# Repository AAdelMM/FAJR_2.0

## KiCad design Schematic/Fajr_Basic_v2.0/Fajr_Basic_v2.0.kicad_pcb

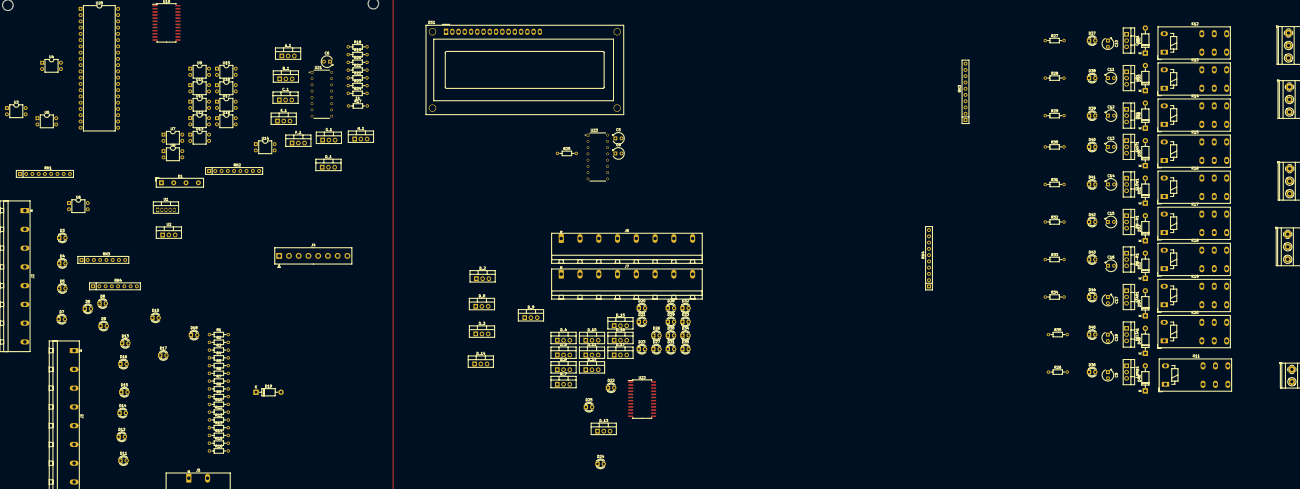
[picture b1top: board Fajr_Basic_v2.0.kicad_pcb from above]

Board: 2 copper layers, 187 parts (0 on the bottom side), 173 nets, no tracks yet.

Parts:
A_1: BD681; TO-220-3_Vertical
B_1: BD681; TO-220-3_Vertical
C5, C6, C8, C9, C10, C11, C12, C13, C14, C15, C16, C17, C18: 104; CP_Radial_Tantal_D4.5mm_P2.50mm
C_1: BD681; TO-220-3_Vertical
Cam1: BD681; TO-220-3_Vertical
D1: BR3A; Diode_Bridge_19.0x3.5x10.0mm_P5.0mm
D3, D4, D5, D6, D7, D8, D9, D10, D11, D12, D13, D14, D15, D16, D17, D18, D20, D21, D22, D23, D24, D25, D26, D27, D28, D29, D30, D31, D32, D33, D34, D35, D36, D37, D38, D39, D40, D41, D42, D43, D44, D45: LED; LED_D3.0mm
D19, D53: 1N4001; D_DO-41_SOD81_P10.16mm_Horizontal
D46, D47, D48, D49, D50, D51, D52, D54, D55: D_DO-41_SOD81_P10.16mm_Horizontal
DELTA1: BD681; TO-220-3_Vertical
DN1: BD681; TO-220-3_Vertical
DS1: WC1602A
D_1, D_2, D_3, D_4, D_5, D_6, D_7, D_8, D_9, D_10, D_11, D_12, D_13, D_14, D_15, D_16, D_17: BD681; TO-220-3_Vertical
E_1: BD681; TO-220-3_Vertical
FAST1: BD681; TO-220-3_Vertical
F_1: BD681; TO-220-3_Vertical
G_1: BD681; TO-220-3_Vertical
H_1: BD681; TO-220-3_Vertical
J2, J3, J6, J7: Screw_Terminal_01x08; PhoenixContact_GMSTBA_2,5_8-G-7,62_1x08_P7.62mm_Horizontal
J4: Display; TE_826576-8_1x08_P3.96mm_Vertical
J5: Screw_Terminal_01x02; PhoenixContact_GMSTB_2,5_2-GF-7,62_1x02_P7.62mm_Horizontal_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
J8: Screw_Terminal_01x02; TerminalBlock_Phoenix_MKDS-1,5-2_1x02_P5.00mm_Horizontal
J9, J10, J11, J12: Screw_Terminal_01x03; TerminalBlock_Phoenix_MKDS-1,5-3-5.08_1x03_P5.08mm_Horizont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
K11: Light; Relay_DPDT_Schrack-RT2-FormC_RM5mm
K12: CAM; Relay_DPDT_Schrack-RT2-FormC_RM5mm
K13: UP; Relay_DPDT_Schrack-RT2-FormC_RM5mm
K14: DN; Relay_DPDT_Schrack-RT2-FormC_RM5mm
K15: Fast; Relay_DPDT_Schrack-RT2-FormC_RM5mm
K16: Slow; Relay_DPDT_Schrack-RT2-FormC_RM5mm
K17: A_UP; Relay_DPDT_Schrack-RT2-FormC_RM5mm
K18: A_DN; Relay_DPDT_Schrack-RT2-FormC_RM5mm
K19, K20: RTE2xxxx; Relay_DPDT_Schrack-RT2-FormC_RM5mm
Lamp1: BD681; TO-220-3_Vertical
PH-N1: BD681; TO-220-3_Vertical
PH-R1: BD681; TO-220-3_Vertical
R1, R2, R3, R4, R5, R6, R7, R8, R9, R10, R11, R12, R13, R14, R15, R16: 1.2k; R_Axial_DIN0204_L3.6mm_D1.6mm_P7.62mm_Horizontal
R17, R18, R19, R20, R21, R22, R23, R24, R26, R27, R28, R29, R30, R31, R32, R33, R34, R35: 1k; R_Axial_DIN0204_L3.6mm_D1.6mm_P7.62mm_Horizontal
R25: 5.1k; R_Axial_DIN0204_L3.6mm_D1.6mm_P7.62mm_Horizontal
RN1, RN2: 2.2k; R_Array_SIP9
RN3, RN4: 820R; R_Array_SIP10
RN3#2, RN4#2: 1k; R_Array_SIP8
SLOW1: BD681; TO-220-3_Vertical
STAR1: BD681; TO-220-3_Vertical
U1: LM2576; TO-220-5_Vertical
U2: LM7805_TO220; TO-220-3_Vertical
U3, U4, U5, U6, U7, U8, U9, U10, U11, U12, U13, U14, U15, U16, U17, U18: PC817; DIP-4_W7.62mm
U19, U22: CD74HC4067M; SOIC-24W_7.5x15.4mm_P1.27mm
U20: ATmega644-20P; DIP-40_W15.24mm
U21, U23: CD4094BE; DIP794W45P254L1969H508Q16
UP1: BD681; TO-220-3_Vertical

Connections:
/7SEG/+5V: C5.1, C6.1, C8.1, DS1.2 (VDD), RN1.1 (common), RN2.1 (common), U2.3 (VO), U19.24 (VCC), U21.15 (OUT_EN), U21.16 (VDD), U23.15 (OUT_EN), U23.16 (VDD)
/7SEG/PD5: U20.19 (PD5), U21.2 (DATA)
/7SEG/PD6: U20.20 (PD6), U21.3 (CLOCK), U23.3 (CLOCK)
/7SEG/PD7: U20.21 (PD7), U21.1 (STRB), U23.1 (STRB)
/7SEG/Q`S: R25.2, U21.10 (QS), U23.2 (DATA)
/CALLS_SINALS/PC7: U20.29 (PC7), U22.1 (COM)
/LCD/PA3: DS1.6 (E), U20.37 (PA3)
/LCD/PD4: DS1.4 (RS), U19.10 (S0), U20.36 (PA4)
/MCU_MAIN/PA5: U19.11 (S1), U20.35 (PA5)
/MCU_MAIN/PA6: U19.14 (S2), U20.34 (PA6)
/MCU_MAIN/PA7: U19.13 (S3), U20.33 (PA7)
/MCU_MAIN/PC6: U19.1 (COM), U20.28 (PC6)
/Movement/+12V: C9.2, C10.2, C11.2, C12.2, C13.2, C14.2, C15.2, C16.2, C17.2, C18.2, D46.1 (K), D47.1 (K), D48.1 (K), D49.1 (K), D50.1 (K), D51.1 (K), D52.1 (K), D53.1 (K), D54.1 (K), D55.1 (K), K11.A1, K12.A1, K13.A1, K14.A1, K15.A1, K16.A1, K17.A1, K18.A1, K19.A1, K20.A1, R26.1, R27.1, R28.1, R29.1, R30.1, R31.1, R32.1, R33.1, R34.1, R35.1, U1.4 (FB), U2.1 (VI)
/Power_circuit/+24: D1.3 (+), D19.2 (A), U1.1 (VIN)
AUX: RN2.5 (R4), U14.4, U19.5 (I4)
DCL: RN2.4 (R3), U13.4, U19.3 (I6)
DNL: RN1.9 (R8), U10.4, U19.20 (I11)
DOP: RN2.3 (R2), U12.4, U19.4 (I5)
FIRE: RN2.6 (R5), U15.4, U19.2 (I7)
FRK: RN1.6 (R5), U7.4, U19.23 (I8)
GND: A_1.3 (E), B_1.3 (E), C5.2, C6.2, C8.2, C_1.3 (E), Cam1.3 (E), D1.1 (-), DELTA1.3 (E), DN1.3 (E), DS1.1 (VSS), DS1.5 (R/W), D_1.3 (E), D_2.3 (E), D_3.3 (E), D_4.3 (E), D_5.3 (E), D_6.3 (E), D_7.3 (E), D_8.3 (E), D_9.3 (E), D_10.3 (E), D_11.3 (E), D_12.3 (E), D_13.3 (E), D_14.3 (E), D_15.3 (E), D_16.3 (E), D_17.3 (E), E_1.3 (E), FAST1.3 (E), F_1.3 (E), G_1.3 (E), H_1.3 (E), Lamp1.3 (E), PH-N1.3 (E), PH-R1.3 (E), R25.1, SLOW1.3 (E), STAR1.3 (E), U1.3 (GND), U1.5 (~ON/OFF), U2.2 (GND), U3.2, U3.3, U4.2, U4.3, U5.2, U5.3, U6.2, U6.3, U7.2, U7.3, U8.2, U8.3, U9.2, U9.3, U10.2, U10.3, U11.2, U11.3, U12.2, U12.3, U13.2, U13.3, U14.2, U14.3, U15.2, U15.3, U16.2, U16.3, U17.2, U17.3, U18.2, U18.3, U19.12 (GND), U19.15 (~E), U21.8 (VSS), U23.8 (VSS), UP1.3 (E)
LOC: RN1.7 (R6), U8.4, U19.22 (I9)
MTR: RN1.5 (R4), U6.4, U19.18 (I13)
unnamed: A_1.1 (B), R17.2
unnamed: A_1.2 (C), J4.1
unnamed: B_1.1 (B), R18.2
unnamed: B_1.2 (C), J4.2
unnamed: C_1.1 (B), R19.2
unnamed: C_1.2 (C), J4.3
unnamed: C10.1, Cam1.2 (C), D37.1 (K), D47.2 (A), K12.A2
unnamed: D3.2 (A), J2.8
unnamed: D3.1 (K), R1.1
unnamed: D4.2 (A), J2.7
unnamed: D4.1 (K), R2.1
unnamed: D5.2 (A), J2.6
unnamed: D5.1 (K), R3.1
unnamed: D6.2 (A), J2.5
unnamed: D6.1 (K), R4.1
unnamed: D7.2 (A), J2.4
unnamed: D7.1 (K), R5.1
unnamed: D8.2 (A), J2.3
unnamed: D8.1 (K), R6.1
unnamed: D9.2 (A), J2.2
unnamed: D9.1 (K), R7.1
unnamed: D10.2 (A), J2.1
unnamed: D10.1 (K), R8.1
unnamed: D11.2 (A), J3.8
unnamed: D11.1 (K), R9.1
unnamed: D12.2 (A), J3.7
unnamed: D12.1 (K), R10.1
unnamed: D13.2 (A), J3.6
unnamed: D13.1 (K), R11.1
unnamed: D14.2 (A), J3.5
unnamed: D14.1 (K), R12.1
unnamed: D15.2 (A), J3.4
unnamed: D15.1 (K), R13.1
unnamed: D16.2 (A), J3.3
unnamed: D16.1 (K), R14.1
unnamed: D17.2 (A), J3.2
unnamed: D17.1 (K), R15.1
unnamed: D18.2 (A), J3.1
unnamed: D18.1 (K), R16.1
unnamed: D19.1 (K), J5.1
unnamed: D20.1 (K), D_17.1 (B)
unnamed: D21.1 (K), D_16.1 (B)
unnamed: D22.1 (K), D_15.1 (B)
unnamed: D23.1 (K), D_14.1 (B)
unnamed: D24.1 (K), D_13.1 (B)
unnamed: D25.1 (K), D_12.1 (B)
unnamed: D26.1 (K), D_11.1 (B)
unnamed: D27.1 (K), D_10.1 (B)
unnamed: D28.1 (K), D_9.1 (B)
unnamed: D29.1 (K), D_8.1 (B)
unnamed: D30.1 (K), D_7.1 (B)
unnamed: D31.1 (K), D_6.1 (B)
unnamed: D32.1 (K), D_5.1 (B)
unnamed: D33.1 (K), D_4.1 (B)
unnamed: D34.1 (K), D_3.1 (B)
unnamed: D35.1 (K), D_2.1 (B)
unnamed: D36.2 (A), R26.2
unnamed: C9.1, D36.1 (K), D46.2 (A), K11.A2, Lamp1.2 (C)
unnamed: D37.2 (A), R27.2
unnamed: D38.2 (A), R28.2
unnamed: C11.1, D38.1 (K), D48.2 (A), K13.A2, UP1.2 (C)
unnamed: D39.2 (A), R29.2
unnamed: C12.1, D39.1 (K), D49.2 (A), DN1.2 (C), K14.A2
unnamed: D40.2 (A), R30.2
unnamed: C13.1, D40.1 (K), D50.2 (A), FAST1.2 (C), K15.A2
unnamed: D41.2 (A), R31.2
unnamed: C14.1, D41.1 (K), D51.2 (A), K16.A2, SLOW1.2 (C)
unnamed: D42.2 (A), R32.2
unnamed: C15.1, D42.1 (K), D52.2 (A), K17.A2, PH-N1.2 (C)
unnamed: D43.2 (A), R33.2
unnamed: C16.1, D43.1 (K), D53.2 (A), K18.A2, PH-R1.2 (C)
unnamed: D44.2 (A), R34.2
unnamed: C17.1, D44.1 (K), D54.2 (A), K19.A2, STAR1.2 (C)
unnamed: D45.2 (A), R35.2
unnamed: C18.1, D45.1 (K), D55.2 (A), DELTA1.2 (C), K20.A2
unnamed: DS1.7 (D0), U23.11 (Q8)
unnamed: DS1.8 (D1), U23.12 (Q7)
unnamed: DS1.9 (D2), U23.13 (Q6)
unnamed: DS1.10 (D3), U23.14 (Q5)
unnamed: DS1.11 (D4), U23.7 (Q4)
unnamed: DS1.12 (D5), U23.6 (Q3)
unnamed: DS1.13 (D6), U23.5 (Q2)
unnamed: DS1.14 (D7), U23.4 (Q1)
unnamed: D_1.1 (B), R20.2
unnamed: D_1.2 (C), J4.4
unnamed: E_1.1 (B), R21.2
unnamed: E_1.2 (C), J4.5
unnamed: F_1.1 (B), R22.2
unnamed: F_1.2 (C), J4.6
unnamed: G_1.1 (B), R23.2
unnamed: G_1.2 (C), J4.7
unnamed: H_1.1 (B), R24.2
unnamed: H_1.2 (C), J4.8
unnamed: J8.1, K11.14, K11.24
unnamed: J8.2, K11.11, K11.21
unnamed: J9.1, K12.11, K12.21
unnamed: J9.2, K12.14, K12.24
unnamed: J9.3, K12.12, K12.22
unnamed: J10.1, K13.11, K13.21, K14.11, K14.21
unnamed: J10.2, K13.14, K13.24
unnamed: J10.3, K14.14, K14.24
unnamed: J11.1, K15.11, K15.21, K16.11, K16.21
unnamed: J11.2, K15.14, K15.24
unnamed: J11.3, K16.14, K16.24
unnamed: J12.1, K17.11, K17.21, K18.11, K18.21
unnamed: J12.2, K17.24
unnamed: J12.3, K18.24
unnamed: R1.2, U3.1
unnamed: R2.2, U4.1
unnamed: R3.2, U5.1
unnamed: R4.2, U6.1
unnamed: R5.2, U7.1
unnamed: R6.2, U8.1
unnamed: R7.2, U9.1
unnamed: R8.2, U10.1
unnamed: R9.2, U11.1
unnamed: R10.2, U12.1
unnamed: R11.2, U13.1
unnamed: R12.2, U14.1
unnamed: R13.2, U15.1
unnamed: R14.2, U16.1
unnamed: R15.2, U17.1
unnamed: R16.2, U18.1
unnamed: U20.11 (GND), U20.31 (GND)
unnamed: R24.1, U21.4 (Q1)
unnamed: R23.1, U21.5 (Q2)
unnamed: R22.1, U21.6 (Q3)
unnamed: R21.1, U21.7 (Q4)
unnamed: R20.1, U21.14 (Q5)
unnamed: R19.1, U21.13 (Q6)
unnamed: R18.1, U21.12 (Q7)
unnamed: R17.1, U21.11 (Q8)
RELAY1: Lamp1.1 (B), RN3.9 (R5.1)
RELAY2: Cam1.1 (B), RN3.7 (R4.1)
RELAY3: RN3.5 (R3.1), UP1.1 (B)
RELAY4: DN1.1 (B), RN3.3 (R2.1)
RELAY5: FAST1.1 (B), RN3.1 (R1.1)
RELAY6: RN4.9 (R5.1), SLOW1.1 (B)
RELAY7: PH-N1.1 (B), RN4.7 (R4.1)
RELAY8: PH-R1.1 (B), RN4.5 (R3.1)
RELAY9: RN4.3 (R2.1), STAR1.1 (B)
RELAY10: DELTA1.1 (B), RN4.1 (R1.1)
S: RN2.9 (R8), U18.4, U19.9 (I0)
SAF: RN2.2 (R1), U11.4, U19.17 (I14)
SDN: RN2.8 (R7), U17.4, U19.7 (I2)
SEL: RN1.2 (R1), U3.4, U20.17 (PD3)
SLIP: RN1.4 (R3), U5.4, U19.19 (I12)
STP: RN1.3 (R2), U4.4, U20.16 (PD2)
SUP: RN2.7 (R6), U16.4, U19.8 (I1)
UPL: RN1.8 (R7), U9.4, U19.21 (I10)

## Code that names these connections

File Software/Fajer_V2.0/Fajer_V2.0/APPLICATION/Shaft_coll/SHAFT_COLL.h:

/*
 * SHAFT_COLL.h
 *
 * Created: 4/22/2023 8:41:10 AM
 *  Author: Ahmed Adel
 */ 


#ifndef SHAFT_COLL_H_
#define SHAFT_COLL_H_

#include "../../MCAL/DIO/DIO.h"
#define A PA4 //S0
#define B PA5 //S1
#define C PA6 //S2
#define D PA7 //S3
#define S 0
#define SUP 1
#define SDN 2
#define OW 3
#define AUX 4
#define DOP 5
#define DCL 6
#define FIRE 7
#define FRK 8
#define LOC 9
#define UPL 10
#define DNL 11
#define SLIP 12
#define MTR 13
#define SAF 14
#define MUX_CTRL_PORT PORTA
#define MUX_CTRL_DDR DDRA
#define MUX_OUTPUT_PIN PINC
#define MUX_OUTPUT_BIT PC6

#define SEL PD3
#define SEL_PIN PIND
#define STP PD2
#define STP_PIN PIND
#define Shaft_input PC6


unsigned char muxData[15] ;
uint8_t shaftInputValue;

int shaftSignal(void);
void sendMuxData(uint8_t *mux);
void init_mux(void);
void set_mux_channel(uint8_t channel);



#endif /* SHAFT_COLL_H_ */

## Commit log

2023-07-16 programming module edited
